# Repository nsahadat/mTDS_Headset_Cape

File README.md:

# mTDS_Headset_Cape
KiCAD design of mTDS headset which communicates to BBB or a PC to send mTDS control signals

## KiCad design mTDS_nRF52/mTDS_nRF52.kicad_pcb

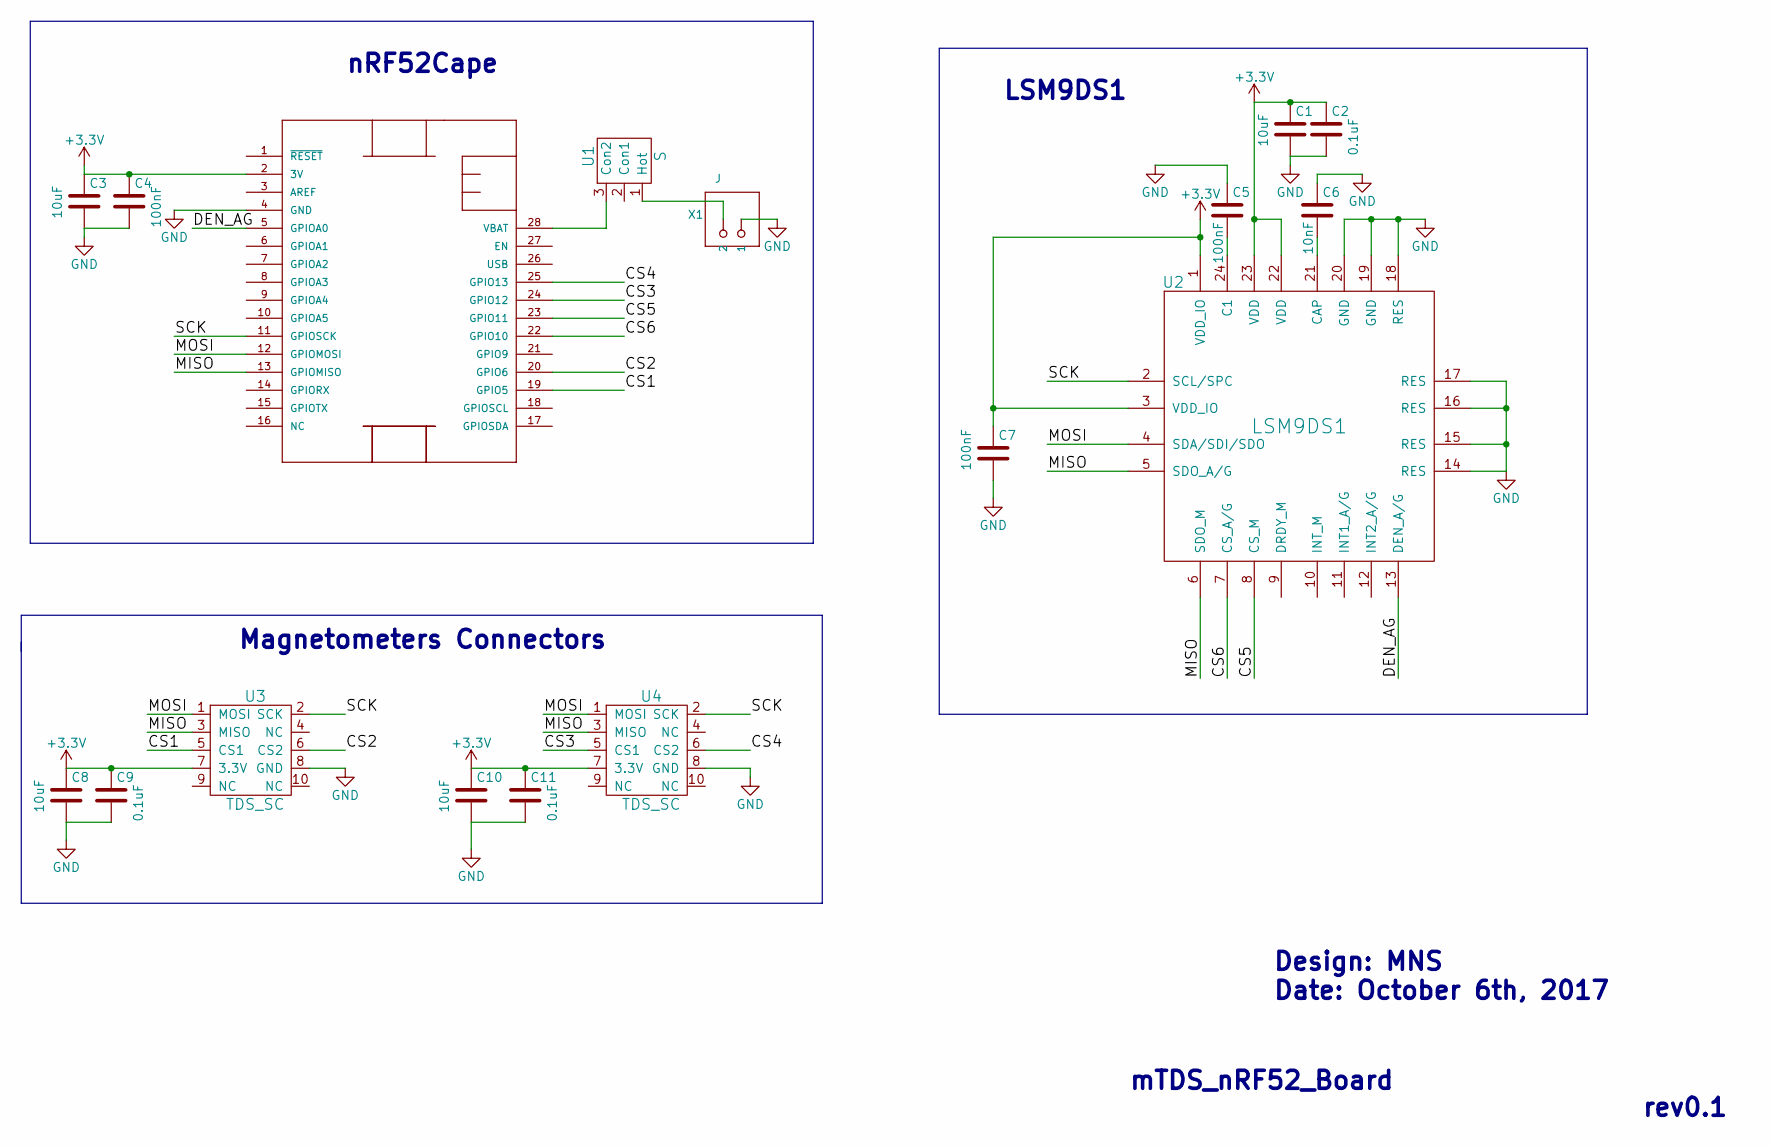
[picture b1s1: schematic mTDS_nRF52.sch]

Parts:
C1, C3, C8, C10: 10uF; C_0603
C2, C9, C11: 0.1uF; C_0603
C4, C5, C7: 100nF; C_0603
C6: 10nF; C_0603
MS1: nRF52; MICROBUILDER_FEATHERWING_NOHOLES
U1: S; switch
U2: LSM9DS1; LSM9DS1B
U3, U4: TDS_SC
X1: J; Bat_Con

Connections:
+3V3: C1.1, C2.1, C3.1, C4.1, C7.1, C8.1, C9.1, C10.1, C11.1, MS1.2 (3V), U2.1 (VDD_IO), U2.3 (VDD_IO), U2.22 (VDD), U2.23 (VDD), U3.7 (3.3V), U4.7 (3.3V)
/CS1: MS1.19 (GPIO5), U3.5 (CS1)
/CS2: MS1.20 (GPIO6), U3.6 (CS2)
/CS3: MS1.24 (GPIO12), U4.5 (CS1)
/CS4: MS1.25 (GPIO13), U4.6 (CS2)
/CS5: MS1.23 (GPIO11), U2.8 (CS_M)
/CS6: MS1.22 (GPIO10), U2.7 (CS_A/G)
/DEN_AG: MS1.5 (GPIOA0), U2.13 (DEN_A/G)
/MISO: MS1.13 (GPIOMISO), U2.5 (SDO_A/G), U2.6 (SDO_M), U3.3 (MISO), U4.3 (MISO)
/MOSI: MS1.12 (GPIOMOSI), U2.4 (SDA/SDI/SDO), U3.1 (MOSI), U4.1 (MOSI)
/SCK: MS1.11 (GPIOSCK), U2.2 (SCL/SPC), U3.2 (SCK), U4.2 (SCK)
GND: C1.2, C2.2, C3.2, C4.2, C5.1, C6.1, C7.2, C8.2, C9.2, C10.2, C11.2, MS1.4 (GND), U2.14 (RES), U2.15 (RES), U2.16 (RES), U2.17 (RES), U2.18 (RES), U2.19 (GND), U2.20 (GND), U3.8 (GND), U4.8 (GND), X1.1
unnamed: C5.2, U2.24 (C1)
unnamed: C6.2, U2.21 (CAP)
unnamed: MS1.28 (VBAT), U1.3 (Con2)
unnamed: U1.1 (Hot), X1.2

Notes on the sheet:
nRF52Cape
LSM9DS1
Magnetometers Connectors
mTDS_nRF52_Board
rev0.1
Design: MNS Date: October 6th, 2017

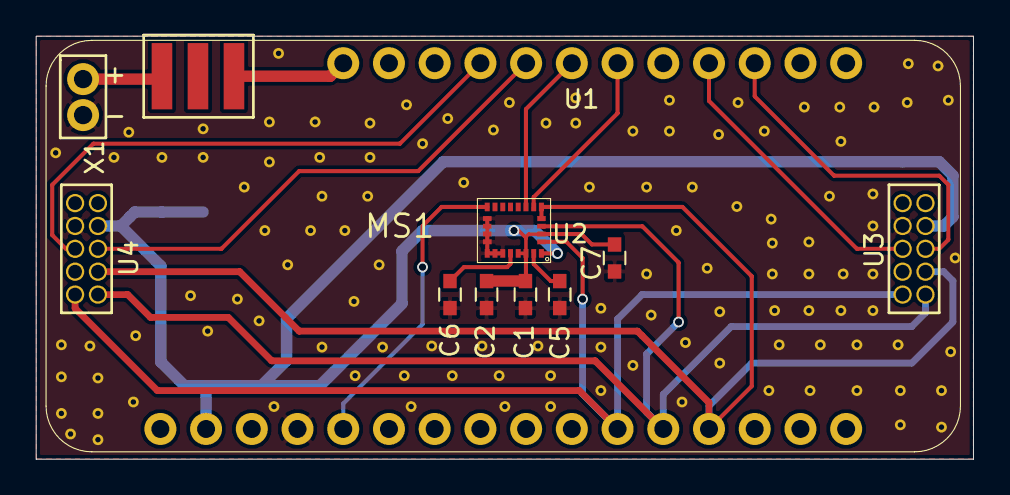
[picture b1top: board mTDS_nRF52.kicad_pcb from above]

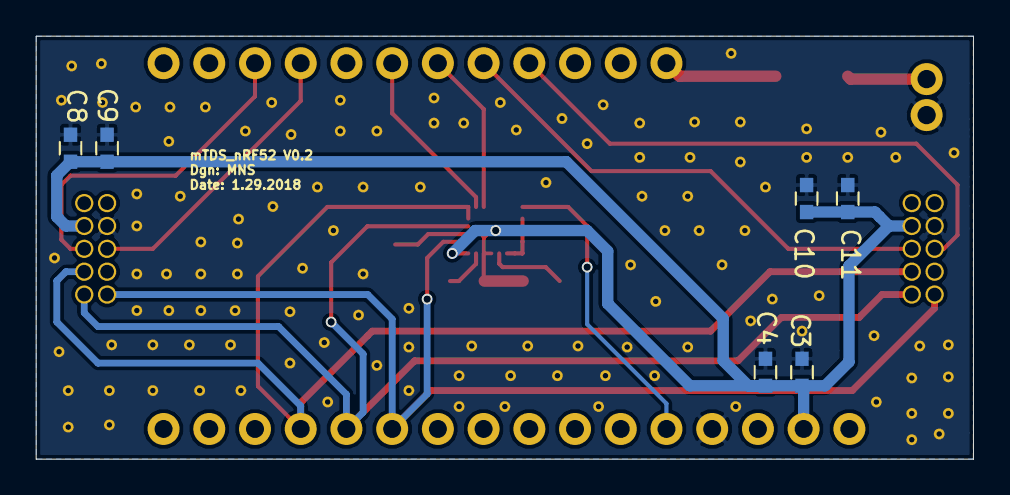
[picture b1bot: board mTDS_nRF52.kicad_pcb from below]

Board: 2 copper layers, 52.1 x 23.5 mm, 17 parts (6 on the bottom side), 16 nets.

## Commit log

2019-10-12 Add files via upload
    This is cape uses nRF52 to receive all the sensor signals to do machine learning to control PC, Wheelchair and smartphone
